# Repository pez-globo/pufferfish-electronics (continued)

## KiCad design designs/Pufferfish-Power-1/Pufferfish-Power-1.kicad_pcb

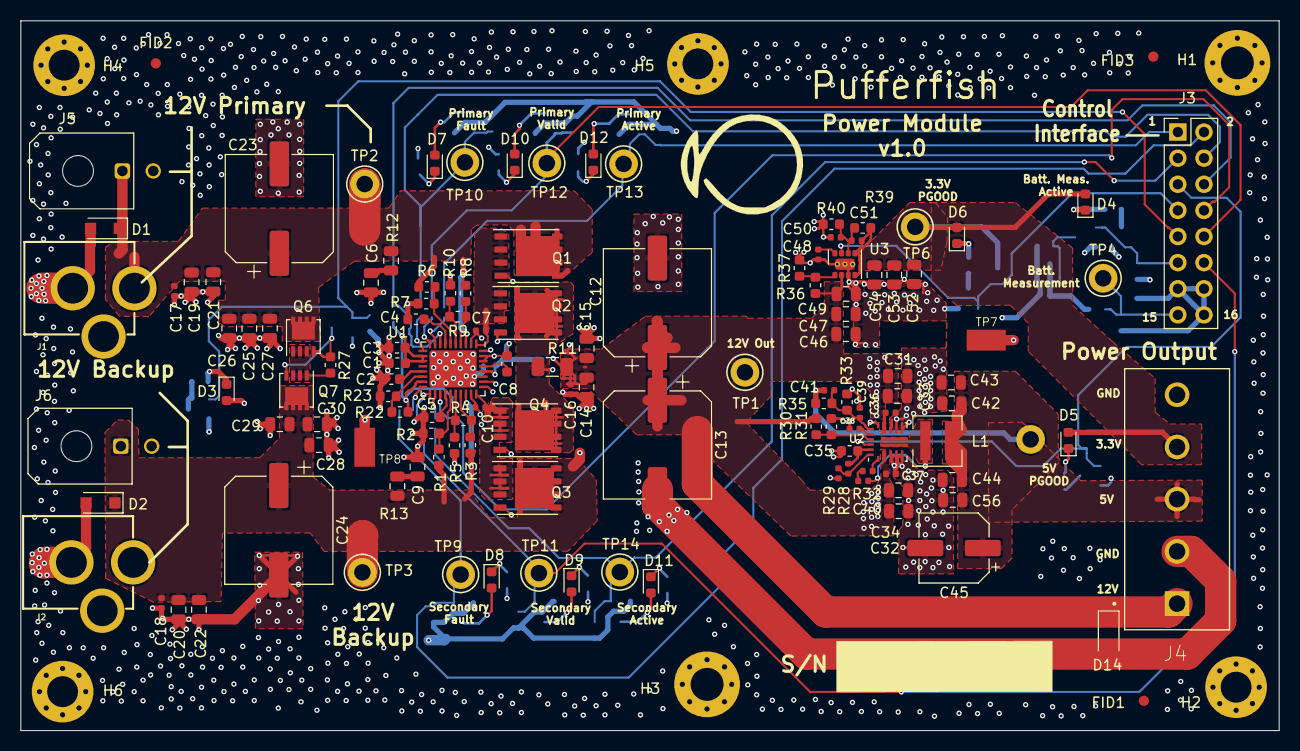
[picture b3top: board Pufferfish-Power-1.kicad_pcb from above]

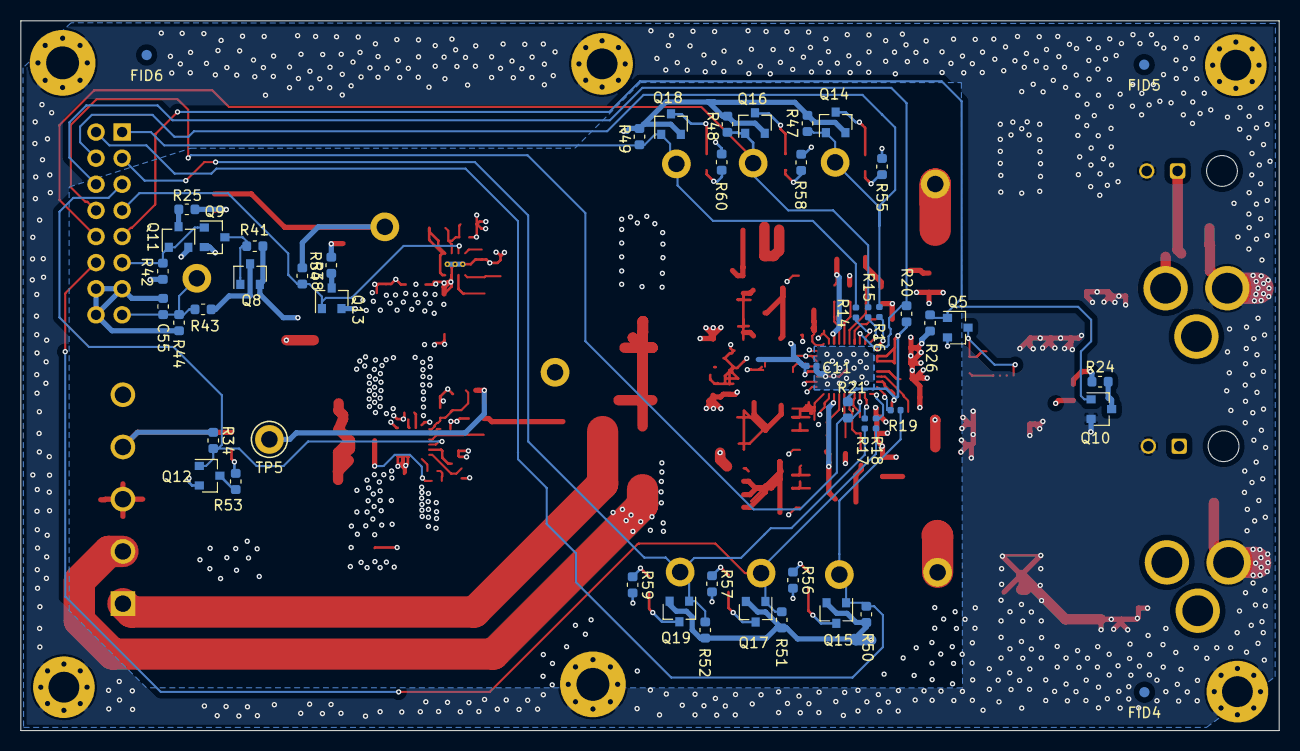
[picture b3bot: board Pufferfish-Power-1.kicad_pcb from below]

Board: 4 copper layers, 122.4 x 69.0 mm, 182 parts (50 on the bottom side), 79 nets.

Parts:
C1, C8, C55: CAP_1uF_35V_X7R_0603; CAP_SMD_0603
C2: CAP_1nF_50V_C0G_0402; CAP_SMD_0603
C3: CAP_100pF_10V_NP0_0402; CAP_SMD_0603
C4, C5: CAP_33nF_25V_X7R_0603; CAP_SMD_0603
C6, C9, C14, C15, C19, C20, C21, C22, C34: CAP_10uF_35V_X5R_0805; CAP_SMD_0805
C7, C10, C38: CAP_47nF_50V_X7R_0402; CAP_SMD_0402
C11, C16, C17, C18, C36, C37, C40: CAP_100nF_50V_X7R_0402; CAP_SMD_0402
C12, C13, C23, C24: CAP_AE_SMD_220uF_25V_8mm; CP_Elec_10x7.9
C25, C26, C27, C28, C29, C30, C31, C32, C33, C42, C43, C44, C46, C47, C49, C52, C53, C54, C56: CAP_22uF_25V_X5R_0805; CAP_SMD_0805
C35: CAP_4.7uF_16V_X6S_0603; CAP_SMD_0603
C39, C50: CAP_1nF_50V_C0G_0402; CAP_SMD_0402
C41, C51: CAP_100pF_10V_NP0_0402; CAP_SMD_0402
C45: CAP_AE_SMD_100uF_10V_6mm; CP_Elec_6.3x5.4
C48: CAP_3.3nF_50V_X7R_0402; CAP_SMD_0402
D1, D2, D14: TVS_15V_SOD123FL-2; D_SOD-123F
D3, D4: LED_SMD_0603_YELLOW; LED_0603_1608Metric
D5, D6: LED_SMD_0603_ORANGE; LED_0603_1608Metric
D7, D8: LED_SMD_0603_RED; LED_0603_1608Metric
D9, D10: LED_SMD_0603_GREEN; LED_0603_1608Metric
D11, D12: LED_SMD_0603_BLUE; LED_0603_1608Metric
FID1, FID2, FID3, FID4, FID5, FID6: Fiducial; Fiducial_1mm_Mask2mm
H1, H3: STANDOFF_ELECTRICAL; MountingHole_3.2mm_M3_Pad_Via
H2, H4, H5, H6: STANDOFF_ELECTRICAL; MountingHole_3mm_Pad_Via
J1, J2: POWER_JACK_PTH
J3: 5103308-3; PinHeader_2x08_P2.54mm_Vertical
J4: Screw_Terminal_01x05; CUI_TB004-508-05BE
J5, J6: Molex_MicroFit_2P; Molex_Micro-Fit_3.0_43045-0200_2x01_P3.00mm_Horizontal
L1: PM2201.122NLT; L_Pulse_PA5001
Q1, Q2, Q3, Q4: SiR158DP; PowerPAK_SO-8_Single
Q5, Q9, Q10, Q11, Q12, Q13: 2N7002E; SOT-23
Q6, Q7: SiSS27DN; Vishay_PowerPAK_1212-8_Single
Q8, Q14, Q15, Q16, Q17, Q18, Q19: TP0610T; SOT-23
R1, R3, R6, R8: RES_768K_0603_SMD; RES_SMD_0603
R2, R7: RES_24K9_0603_SMD; RES_SMD_0603
R4, R9: RES_3K65_0603_SMD; RES_SMD_0603
R5, R10: RES_36K5_0603_SMD; RES_SMD_0603
R11: CSNL1206FT3L00; RES_SMD_1206
R12, R13: RES_1R2_0805_SMD; RES_SMD_0805
R14, R15, R16, R17, R18, R19, R32: RES_0R_0402_SMD; RES_SMD_0402
R20, R21, R22, R23, R26, R31, R33, R34, R37, R38, R40, R41, R42, R44, R47, R48, R49, R50, R51, R52: RES_10K_0603_SMD; RES_SMD_0603
R24, R25, R53, R54, R55, R56, R57, R58, R59, R60: RES_330R_0603_SMD; RES_SMD_0603
R27: RES_100K_0603_SMD; RES_SMD_0603
R28: RES_62K_0402_SMD; RES_SMD_0402
R29: RES_51K_0402_SMD; RES_SMD_0402
R30, R43: RES_47K_0603_SMD; RES_SMD_0603
R35, R36: RES_73K2_0603_SMD; RES_SMD_0603
R39: RES_31K6_0603_SMD; RES_SMD_0603
TP1, TP2, TP3, TP5, TP6: TP_TH_KEYSTONE_5010; TestPoint_Keystone_5010-5014_Multipurpose
TP4, TP9, TP10, TP11, TP12, TP13, TP14: TP_TH_KEYSTONE_5126; TestPoint_Keystone_5010-5014_Multipurpose
TP7, TP8: TP_SMT_KEYSTONE_5019; TP380X203
U1: LTC4421IUHE; QFN-36-1EP_5x6mm_P0.5mm_EP3.6x4.6mm
U2: TPS568215RNN; Texas_RNN0018A
U3: TPS82130; Texas_SIL0008D_MicroSiP-8-1EP_2.8x3mm_P0.65mm_EP1.1x1.9mm_T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

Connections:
3V3-PGOOD: J3.7, Q13.1, R38.2, U3.7
/3.3V Buck/3V3-EN: R36.2, R37.1, U3.1
/3.3V Buck/3V3-FB: C50.1, C51.2, R39.2, R40.1, U3.6
/3.3V Buck/3V3-SS: C48.1, U3.8
/5V Buck/5V-BUCK-BOOT: R32.1, U2.1
/5V Buck/5V-BUCK-SW: C40.1, L1.1, U2.6, U2.7
/5V Buck/5V-EN: R30.2, R31.1, U2.15
/5V Buck/5V-FB: C39.1, C41.2, R33.1, R35.2, U2.13
/5V Buck/5V-MODE: R28.2, R29.1, U2.18
/5V Buck/5V-SS: C38.1, U2.14
/Input Connectors/CHARGER-DIODE: Q6.1, Q6.2, Q6.3, Q7.1, Q7.2, Q7.3, R27.1
/Input Connectors/CHARGER-GATE: Q5.3, Q6.4, Q7.4, R27.2
/Interface/BAT-MEAS-ANALOG: C55.1, J3.15, R43.2, R44.1, TP4.1
/Interface/BAT-MEAS-EN: J3.11, Q9.1, Q11.1, R42.1
/LTC4221/LTC4421-CPO: C8.2, U1.33
/LTC4221/LTC4421-GATE1: C7.1, Q1.4, Q2.4, U1.2
/LTC4221/LTC4421-GATE2: C10.1, Q3.4, Q4.4, U1.27
/LTC4221/LTC4421-OV1: R6.2, R7.1, U1.6
/LTC4221/LTC4421-OV2: R1.2, R2.1, U1.23
/LTC4221/LTC4421-QUAL: C2.1, U1.15
/LTC4221/LTC4421-RETRY: R22.2, R23.1, U1.16
/LTC4221/LTC4421-SENSE: Q2.5, Q4.5, R11.2, U1.29, U1.36
/LTC4221/LTC4421-SRC1: C7.2, Q1.1, Q1.2, Q1.3, Q2.1, Q2.2, Q2.3, U1.1
/LTC4221/LTC4421-SRC2: C10.2, Q3.1, Q3.2, Q3.3, Q4.1, Q4.2, Q4.3, U1.28
/LTC4221/LTC4421-TMR1: C4.1, U1.7
/LTC4221/LTC4421-TMR2: C5.1, U1.22
/LTC4221/LTC4421-UVF1: R8.2, R9.1, U1.4
/LTC4221/LTC4421-UVF2: R3.2, R4.1, U1.25
/LTC4221/LTC4421-UVR1: R9.2, R10.1, U1.5
/LTC4221/LTC4421-UVR2: R4.2, R5.1, U1.24
BAT-CHARGE-EN: J3.9, Q5.1, Q10.1, R26.1
GND: C1.2, C2.2, C3.2, C4.2, C5.2, C6.2, C9.2, C11.2, C12.2, C13.2, C14.2, C15.2, C16.2, C17.2, C18.2, C19.2, C20.2, C21.2, C22.2, C23.2, C24.2, C25.2, C26.2, C27.2, C28.2, C29.2, C30.2, C31.2, C32.2, C33.2, C34.2, C35.2, C36.2, C37.2, C38.2, C39.2, C42.2, C43.2, C44.2, C45.2, C46.2, C47.2, C48.2, C49.2, C50.2, C52.2, C53.2, C54.2, C55.2, C56.2, D1.2, D2.2, D14.2, H1.1, H2.1, H3.1, H4.1, H5.1, H6.1, J1.GND, J2.GND, J3.13, J3.14, J3.16, J4.2, J4.5, J5.2, J6.2, Q5.2, Q9.2, Q10.2, Q11.2, Q12.2, Q13.2, R2.2, R5.2, R7.2, R10.2, R23.2, R26.2, R29.2, R31.2, R33.2, R37.2, R40.2, R42.2, R44.2, R55.2, R56.2, R57.2, R58.2, R59.2, R60.2, TP7.1, TP8.1, U1.31, U1.37, U2.3, U2.4, U2.5, U2.8, U2.9, U2.10, U2.12, U3.3, U3.9
INTVCC-LTC4421: C1.1, C3.1, R20.1, R21.1, R22.1, U1.12, U1.13, U1.17
LTC4421-PWR-nCH1: J3.1, Q18.1, R14.1, R49.2, TP13.1
LTC4421-PWR-nCH2: J3.3, Q19.1, R17.1, R52.2, TP14.1
LTC4421-PWR-nDISABLE1: J3.6, R20.2, U1.8
LTC4421-PWR-nDISABLE2: J3.8, R21.2, U1.21
LTC4421-PWR-nFAULT1: J3.4, Q14.1, R16.1, R47.2, TP10.1
LTC4421-PWR-nFAULT2: J3.2, Q15.1, R19.1, R50.2, TP9.1
LTC4421-PWR-nVALID1: J3.10, Q16.1, R15.1, R48.2, TP12.1
LTC4421-PWR-nVALID2: J3.12, Q17.1, R18.1, R51.2, TP11.1
unnamed: C6.1, R12.2
unnamed: C9.1, R13.2
unnamed: C40.2, R32.2
unnamed: D3.1, R24.1
unnamed: D4.1, R25.1
unnamed: D5.1, R53.1
unnamed: D6.1, R54.1
unnamed: D7.1, R55.1
unnamed: D7.2, Q14.3
unnamed: D8.1, R56.1
unnamed: D8.2, Q15.3
unnamed: D9.1, R57.1
unnamed: D9.2, Q17.3
unnamed: D10.1, R58.1
unnamed: D10.2, Q16.3
unnamed: D11.1, R59.1
unnamed: D11.2, Q19.3
unnamed: D12.1, R60.1
unnamed: D12.2, Q18.3
unnamed: Q8.1, Q9.3, R41.2
unnamed: Q8.3, R43.1
unnamed: Q10.3, R24.2
unnamed: Q11.3, R25.2
unnamed: Q12.3, R53.2
unnamed: Q13.3, R54.2
unnamed: R14.2, U1.9
unnamed: R15.2, U1.10
unnamed: R16.2, U1.11
unnamed: R17.2, U1.20
unnamed: R18.2, U1.19
unnamed: R19.2, U1.18
VBUCK-INT-5V: C35.1, R28.1, U2.17
VIN-BACKUP-12V0: C18.1, C20.1, C22.1, C24.1, C28.1, C29.1, C30.1, D2.1, J2.PWR, J6.1, Q3.5, Q7.5, Q8.2, R1.1, R3.1, R13.1, R41.1, TP3.1, U1.26
VIN-PRIMARY-12V0: C17.1, C19.1, C21.1, C23.1, C25.1, C26.1, C27.1, D1.1, J1.PWR, J5.1, Q1.5, Q6.5, R6.1, R8.1, R12.1, TP2.1, U1.3
VSYS-3V3: C51.1, C52.1, C53.1, C54.1, D3.2, D4.2, D5.2, D6.2, J4.4, Q14.2, Q15.2, Q16.2, Q17.2, Q18.2, Q19.2, R34.1, R38.1, R39.1, R47.1, R48.1, R49.1, R50.1, R51.1, R52.1, TP6.1, U3.4, U3.5
VSYS-5V0: C41.1, C42.1, C43.1, C44.1, C45.1, C56.1, J4.3, L1.2, R35.1, TP5.1
VSYS-5V0-PGOOD: J3.5, Q12.1, R34.2, U2.16
VSYS-12V0: C8.1, C11.1, C12.1, C13.1, C14.1, C15.1, C16.1, C31.1, C32.1, C33.1, C34.1, C36.1, C37.1, C46.1, C47.1, C49.1, D14.1, J4.1, R11.1, R30.1, R36.1, TP1.1, U1.30, U1.32, U1.34, U1.35, U2.2, U2.11, U3.2

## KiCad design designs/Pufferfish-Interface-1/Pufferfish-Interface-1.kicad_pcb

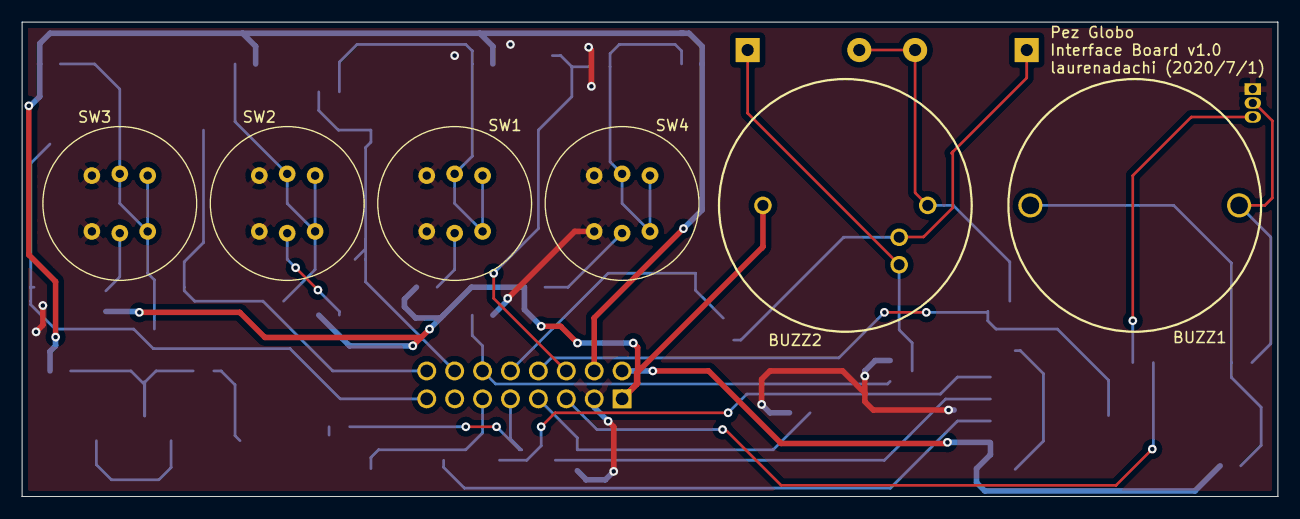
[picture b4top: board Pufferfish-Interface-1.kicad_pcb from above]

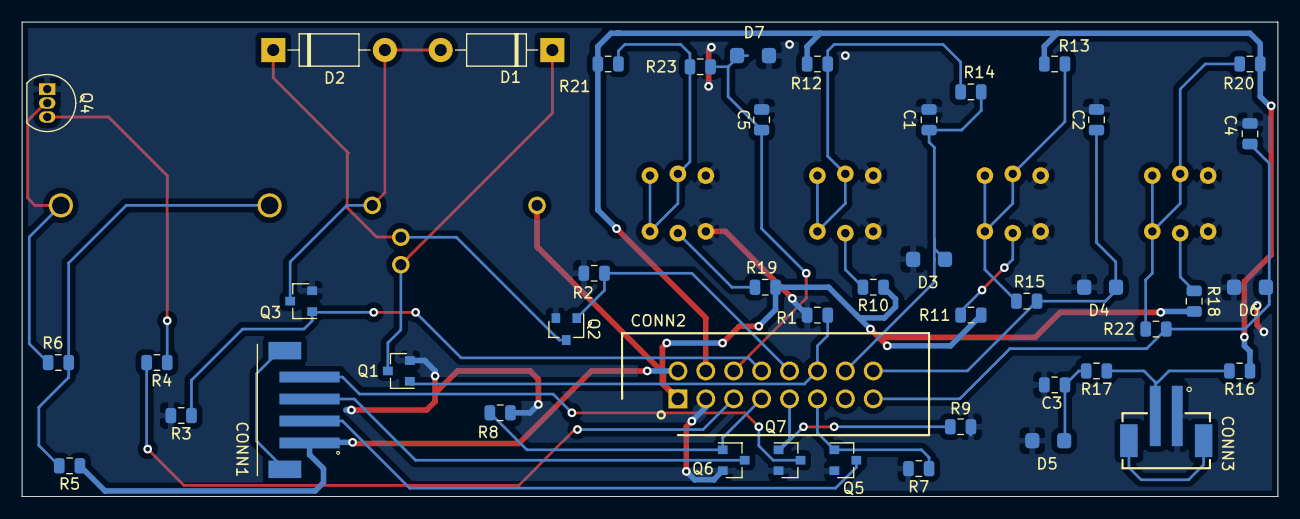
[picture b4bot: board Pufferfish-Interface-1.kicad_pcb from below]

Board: 2 copper layers, 114.3 x 43.2 mm, 51 parts (45 on the bottom side), 36 nets.

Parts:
BUZZ1: BUZZER; Buzzer_PS1927P02
BUZZ2: BUZZER-MALLORY; Buzzer-MSS5MMG
C1, C2, C3, C4, C5: 0.1uF; CAP_SMD_0805
CONN1: B4B-PH-SM4-TB(LF)(SN); JST_B4B-PH-SM4-TB
CONN2: 5103308-3; SHDR16W66P254_2X8
CONN3: B2B-PH-SM4-TB(LF)(SN); JST_B2B-PH-SM4-TB
D1, D2: 1N4001; D_DO-41_SOD81_P10.16mm_Horizontal
D3, D4, D5, D6, D7: SMF3.3; D_TVS_SMF3.3
Q1, Q2, Q3: DMN10H220L; SOT-23
Q4: 2SC1815; TO-92_Inline
Q5, Q6, Q7: 2N7002E; SOT-23
R1, R2, R3, R4, R5, R6, R7, R8, R9, R10, R11, R12, R13, R14, R15, R16, R17, R18, R19, R20, R21, R22, R23: RES_SMD_0805
SW1, SW2, SW3, SW4: SW_SPST_LED; SW_SPST_TC013

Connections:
3.3V: CONN2.4, R12.1, R13.1, R16.1, R20.1, R21.1
5V: BUZZ2.1, CONN2.1, R10.1, R11.1, R18.1, R19.1
+12V: CONN1.1, CONN2.2, R5.1
ALARM1_HIGH: CONN2.12, Q1.1, R1.1
ALARM1_LOW: CONN2.8, Q3.1, R3.1
ALARM1_MED: CONN2.10, Q2.1, R2.1
ALARM2_CNTRL: CONN2.5, R4.2
GND: C1.2, C2.2, C3.2, C4.2, C5.2, CONN2.3, CONN3.1, D3.2, D4.2, D5.2, D6.2, D7.2, Q1.2, Q2.2, Q3.2, Q4.1, Q5.2, Q6.2, Q7.2, R1.2, R2.2, R3.2, R7.2, R8.2, R9.2, SW1.2, SW2.2, SW3.2, SW4.2
LEDB_EN: CONN2.9, Q7.1, R9.1
LEDG_EN: CONN2.11, Q5.1, R7.1
LEDR_EN: CONN2.7, Q6.1, R8.1
unnamed: BUZZ1.1, R5.2, R6.1
unnamed: BUZZ1.2, Q4.2, R6.2
unnamed: BUZZ2.2, D1.1, Q1.3
unnamed: BUZZ2.3, D2.1, Q2.3
unnamed: BUZZ2.4, D1.2, D2.2, Q3.3
unnamed: CONN1.2, Q5.3
unnamed: CONN1.3, Q6.3
unnamed: CONN1.4, Q7.3
unnamed: CONN1.5, CONN1.6
unnamed: CONN3.2, R16.2, R17.1
unnamed: CONN3.3, CONN3.4
unnamed: Q4.3, R4.1
unnamed: R10.2, SW1.4
unnamed: R11.2, SW2.4
unnamed: R12.2, R14.1, SW1.1, SW1.3
unnamed: R13.2, R15.1, SW2.1, SW2.3
unnamed: R18.2, SW3.4
unnamed: R19.2, SW4.4
unnamed: R20.2, R22.1, SW3.1, SW3.3
unnamed: R21.2, R23.1, SW4.1, SW4.3
SET_ALARM_EN: C1.1, CONN2.14, D3.1, R14.2
SET_EXTRA1: C4.1, CONN2.15, D6.1, R22.2
SET_EXTRA2: C5.1, CONN2.6, D7.1, R23.2
SET_LOCK: C2.1, CONN2.16, D4.1, R15.2
SET_PWR_ON_OFF: C3.1, D5.1, R17.2

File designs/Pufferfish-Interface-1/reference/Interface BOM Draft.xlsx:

| Name | datasheet | footprint |  | digikey | Notes
Alarm 1 (reg) | MSS5MMG | https://www.mspindy.com/Specifications/MSS5MMG.pdf | through-hole, hole locations specified on datasheet |  | https://www.digikey.com/product-detail/en/mallory-sonalert-p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
Alarm 2 (Sys) | PS1927P02 | https://product.tdk.com/info/en/catalog/datasheets/piezoelec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 | Through-hole, hole locations specified on datasheet | Buzzer_PS1927P02 | https://www.digikey.com/product-detail/en/tdk-corporation/PS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
Alarm 2 (reg) diodes | 1N4001 | https://www.vishay.com/docs/88503/1n4001.pdf | https://www.mouser.com/ProductDetail/ON-Semiconductor/1N4001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 |  | https://www.digikey.com/product-detail/en/on-semiconductor/1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 | 0805 Si diodes
Resistors | misc | / | Pufferfish:RES_SMD_0805 |  |  | 0805 SMD RES
MOSFETs (Digital) | 2N7002E | https://www.vishay.com/docs/70860/70860.pdf | Package_TO_SOT_SMD:SOT-23 |  | https://www.digikey.com/product-detail/en/vishay-siliconix/2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
BJT (Sys Alarm2) | KSC1815 | https://www.onsemi.com/pub/Collateral/KSC1815-D.pdf | Package_TO_SOT_THT:TO-92_Inline |  | https://product.tdk.com/info/en/catalog/datasheets/piezoelec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 | C1815
MOSFETs (Reg Alarm 1) | DMN10H220L | https://www.diodes.com/assets/Datasheets/DMN10H220L.pdf | Package_TO_SOT_THT:TO-92_Inline |  | https://www.digikey.com/product-detail/en/diodes-incorporate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
Push switches (Front, SMD) | TC013-N11AR3KKK3UBXX | https://www.mouser.com/datasheet/2/435/tc013%20series-1288144.pdf | Through-hole, hole locations specified on datasheet |  | https://www.mouser.com/ProductDetail/Well-Buying/TC013-N11AR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 | Many varieties, can have diff colors, etc
ESD Diode | SMF3.3 | https://www.littelfuse.com/~/media/electronics/datasheets/tv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 | Specified in datasheet, SMD |  | https://www.digikey.com/product-detail/en/littelfuse-inc/SMF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
Connector to LEDs | B4B-PH-SM4-TB(LF)(SN) | See B2B, same but w/ 4 ports
LEDs | 5060BRG4 LED RGB Strip | http://cdn.sparkfun.com/datasheets/Components/LED/5060BRG4.pdf |  |  | https://www.sparkfun.com/products/12023?_ga=2.265891407.1107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
Capacitors | 0.1uF | / | In library
Push switches (Back, QuickConnect) | TBD, any quickconnect switch can be put into the JST connector via JST F, wires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 |  |  |  | https://www.digikey.com/product-detail/en/cw-industries/GPB5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
Connector (Back Push to Wire) | 190160099 | https://www.molex.com/webdocs/datasheets/pdf/en-us/019016009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 | n/a |  | https://www.digikey.com/product-detail/en/molex/0190160099/W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 | 0.187" tab thickness
Connector (Wire to PCB Conn) | PHR-2 | http://www.jst-mfg.com/product/pdf/eng/ePH.pdf | n/a |  | https://www.digikey.com/product-detail/en/jst-sales-america-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 | JST F
Connector (On PCB) | B2B-PH-SM4-TB(LF)(SN) | https://www.digikey.com/product-detail/en/jst-sales-america-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 | https://www.snapeda.com/parts/B2B-PH-SM4-TB(LF)(SN)/JST/view-part/ |  |  | JST M
Connector to Control Board | 5103308-3 |  | In library
